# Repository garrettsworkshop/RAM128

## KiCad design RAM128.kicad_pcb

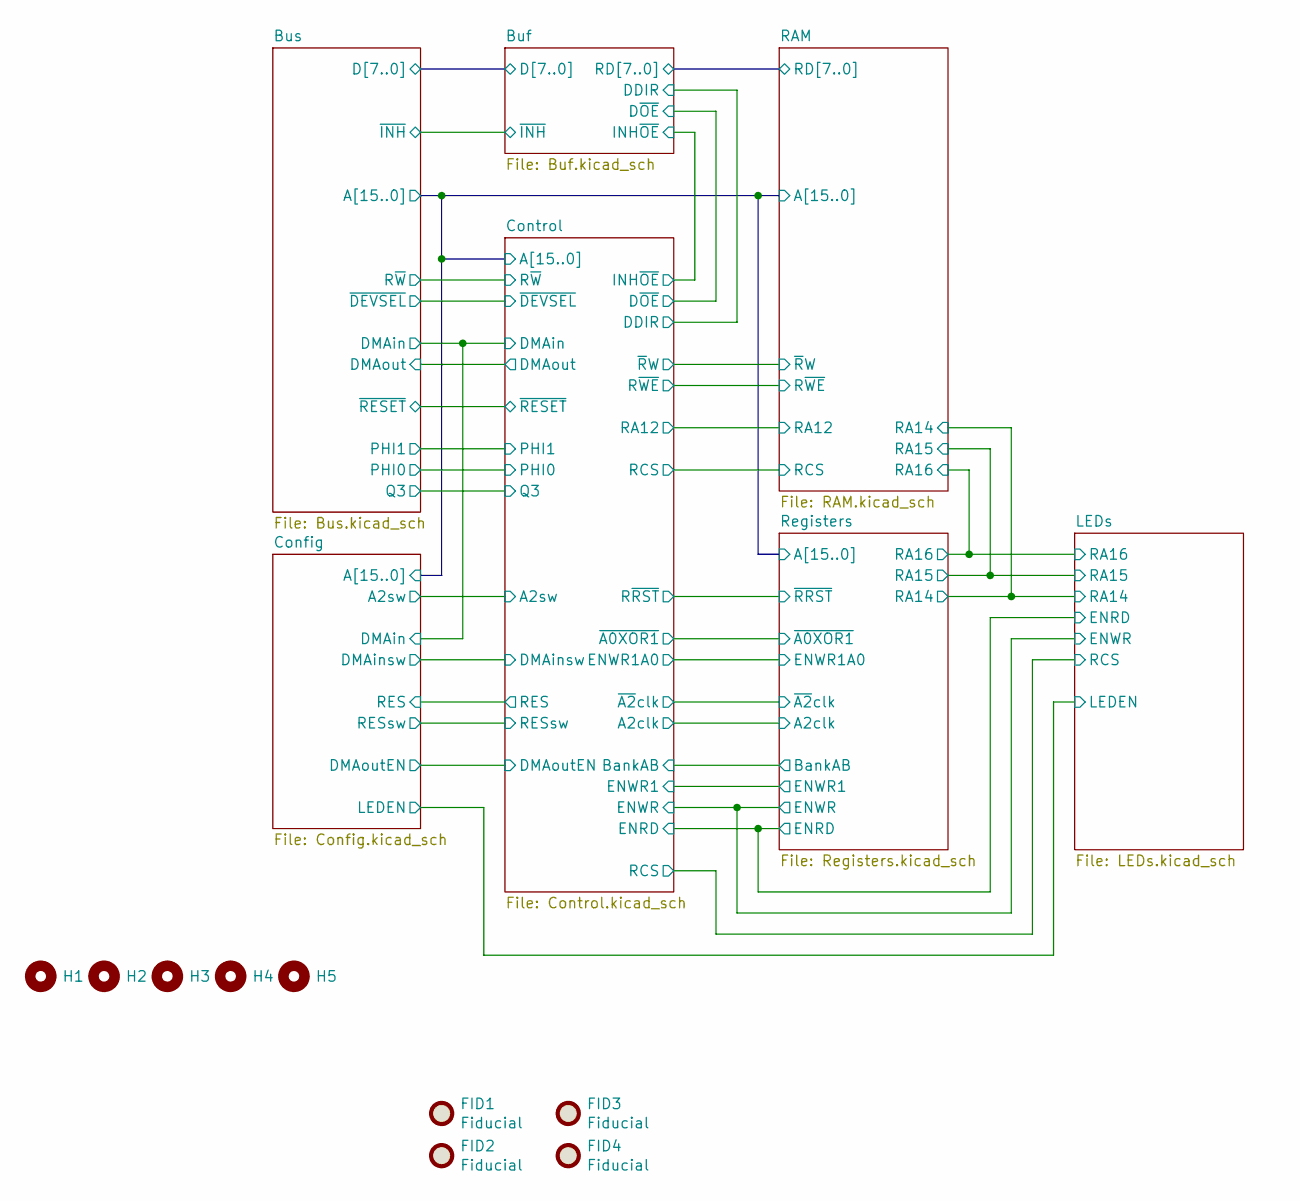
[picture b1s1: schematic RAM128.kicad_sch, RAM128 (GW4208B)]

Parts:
FID1, FID2, FID3, FID4: Fiducial
H1, H2, H3, H4, H5: PasteHole_1.152mm_NPTH

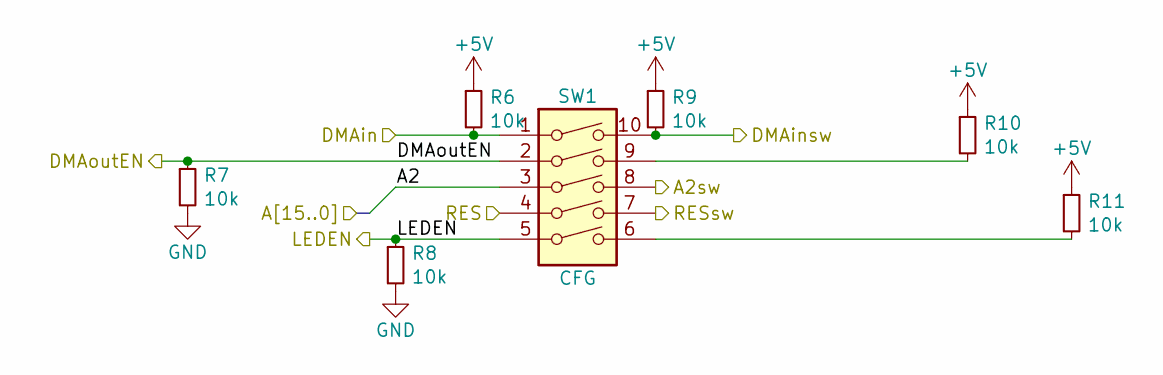
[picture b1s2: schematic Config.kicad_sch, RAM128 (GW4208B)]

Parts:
R6, R7, R8, R9, R10, R11: 10k; R_0603; LCSC Part C17560
SW1: CFG; SW_DIP_SPSTx05_Slide_DSHP05TS_P1.27mm

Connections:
+5V: R6.1, R9.1, R10.1, R11.1; also elsewhere on the board
/Bus/A2: SW1.3; also elsewhere on the board
/Config/A2sw: SW1.8; also elsewhere on the board
/Config/DMAinsw: R9.2, SW1.10; also elsewhere on the board
/Config/DMAoutEN: R7.1, SW1.2; also elsewhere on the board
/Config/LEDEN: R8.1, SW1.5; also elsewhere on the board
/Config/RES: SW1.4; also elsewhere on the board
/Config/RESsw: SW1.7; also elsewhere on the board
/Control/DMAin: R6.2, SW1.1; also elsewhere on the board
GND: R7.2, R8.2; also elsewhere on the board
unnamed: R10.2, SW1.9
unnamed: R11.2, SW1.6

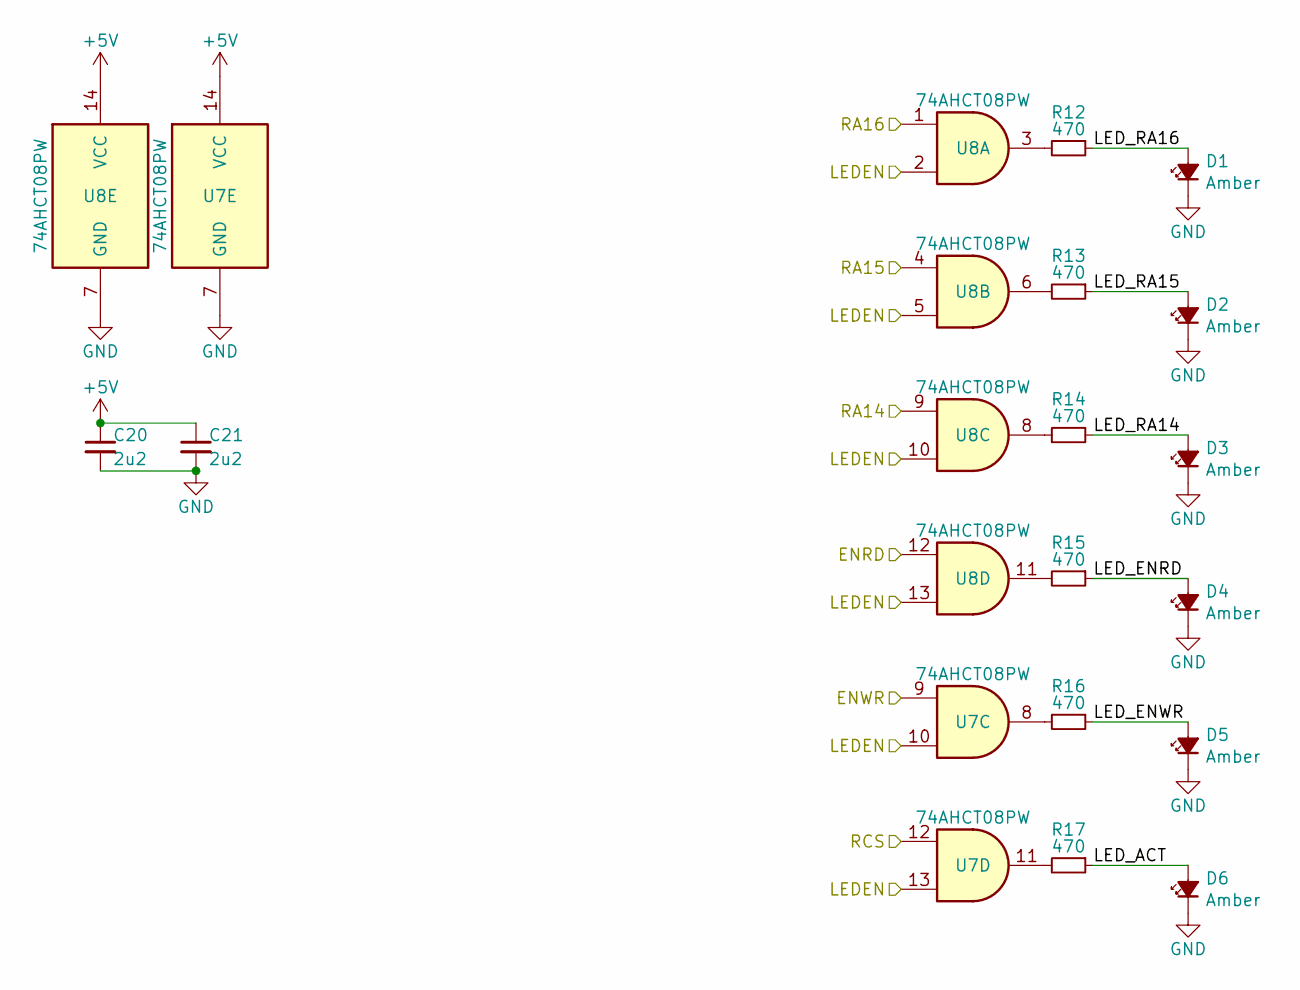
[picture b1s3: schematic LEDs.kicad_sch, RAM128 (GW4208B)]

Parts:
C20, C21: 2u2; C_0603; LCSC Part C23630
D1, D2, D3, D4, D5, D6: Amber; LED_0805; LCSC Part C284932
R12, R13, R14, R15, R16, R17: 470; R_0805
U7, U8: 74AHCT08PW; TSSOP-14_4.4x5mm_P0.65mm; LCSC Part C155175

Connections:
+5V: C20.1, C21.1, U7.14 (VCC), U8.14 (VCC); also elsewhere on the board
/Config/LEDEN: U7.10, U7.13, U8.2, U8.5, U8.10, U8.13; also elsewhere on the board
/Control/ENRD: U8.12; also elsewhere on the board
/Control/ENWR: U7.9; also elsewhere on the board
/Control/RCS: U7.12; also elsewhere on the board
/LEDs/LED_ACT: D6.2 (A), R17.1
/LEDs/LED_ENRD: D4.2 (A), R15.1
/LEDs/LED_ENWR: D5.2 (A), R16.1
/LEDs/LED_RA14: D3.2 (A), R14.1
/LEDs/LED_RA15: D2.2 (A), R13.1
/LEDs/LED_RA16: D1.2 (A), R12.1
/LEDs/RA14: U8.9; also elsewhere on the board
/LEDs/RA15: U8.4; also elsewhere on the board
/LEDs/RA16: U8.1; also elsewhere on the board
GND: C20.2, C21.2, D1.1 (K), D2.1 (K), D3.1 (K), D4.1 (K), D5.1 (K), D6.1 (K), U7.7 (GND), U8.7 (GND); also elsewhere on the board
unnamed: R12.2, U8.3
unnamed: R13.2, U8.6
unnamed: R14.2, U8.8
unnamed: R15.2, U8.11
unnamed: R16.2, U7.8
unnamed: R17.2, U7.11

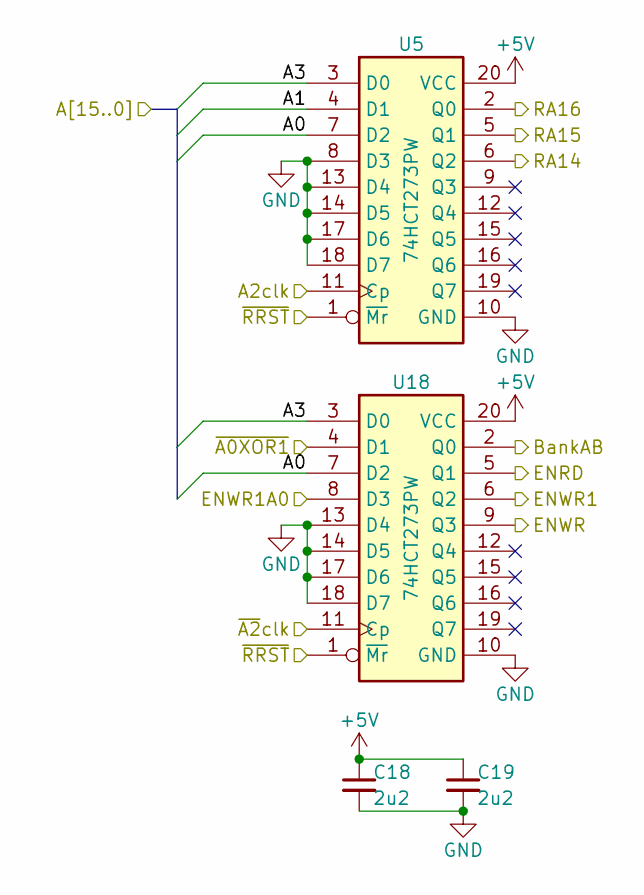
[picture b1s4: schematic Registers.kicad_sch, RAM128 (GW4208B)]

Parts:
C18, C19: 2u2; C_0603; LCSC Part C23630
U5, U18: 74HCT273PW; TSSOP-20_4.4x6.5mm_P0.65mm

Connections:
+5V: C18.1, C19.1, U5.20 (VCC), U18.20 (VCC); also elsewhere on the board
/Bus/A0: U5.7 (D2), U18.7 (D2); also elsewhere on the board
/Bus/A1: U5.4 (D1); also elsewhere on the board
/Bus/A3: U5.3 (D0), U18.3 (D0); also elsewhere on the board
/Control/A2clk: U5.11 (Cp); also elsewhere on the board
/Control/BankAB: U18.2 (Q0); also elsewhere on the board
/Control/ENRD: U18.5 (Q1); also elsewhere on the board
/Control/ENWR: U18.9 (Q3); also elsewhere on the board
/Control/ENWR1: U18.6 (Q2); also elsewhere on the board
/Control/ENWR1A0: U18.8 (D3); also elsewhere on the board
/Control/R~RST: U5.1 (~Mr), U18.1 (~Mr); also elsewhere on the board
/Control/~A0XOR1: U18.4 (D1); also elsewhere on the board
/Control/~A2clk: U18.11 (Cp); also elsewhere on the board
/LEDs/RA14: U5.6 (Q2); also elsewhere on the board
/LEDs/RA15: U5.5 (Q1); also elsewhere on the board
/LEDs/RA16: U5.2 (Q0); also elsewhere on the board
GND: C18.2, C19.2, U5.8 (D3), U5.10 (GND), U5.13 (D4), U5.14 (D5), U5.17 (D6), U5.18 (D7), U18.10 (GND), U18.13 (D4), U18.14 (D5), U18.17 (D6), U18.18 (D7); also elsewhere on the board

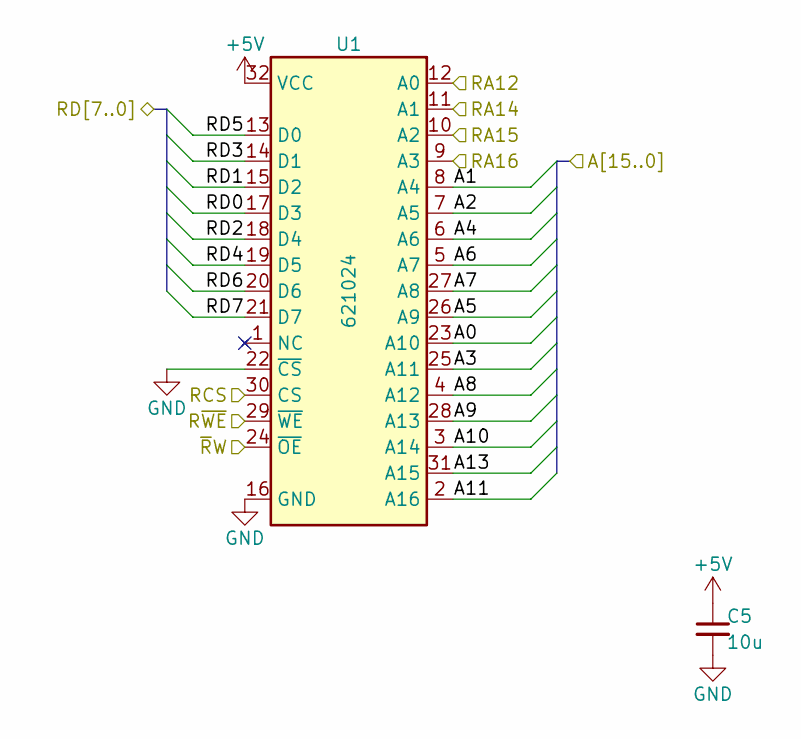
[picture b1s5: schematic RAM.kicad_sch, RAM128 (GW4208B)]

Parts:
C5: 10u; C_0805; LCSC Part C15850
U1: 621024; SOP-32_450mil; LCSC Part C397875

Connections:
+5V: C5.1, U1.32 (VCC); also elsewhere on the board
/Buf/RD0: U1.17 (D3); also elsewhere on the board
/Buf/RD1: U1.15 (D2); also elsewhere on the board
/Buf/RD2: U1.18 (D4); also elsewhere on the board
/Buf/RD3: U1.14 (D1); also elsewhere on the board
/Buf/RD4: U1.19 (D5); also elsewhere on the board
/Buf/RD5: U1.13 (D0); also elsewhere on the board
/Buf/RD6: U1.20 (D6); also elsewhere on the board
/Buf/RD7: U1.21 (D7); also elsewhere on the board
/Bus/A0: U1.23 (A10); also elsewhere on the board
/Bus/A1: U1.8 (A4); also elsewhere on the board
/Bus/A2: U1.7 (A5); also elsewhere on the board
/Bus/A3: U1.25 (A11); also elsewhere on the board
/Bus/A4: U1.6 (A6); also elsewhere on the board
/Bus/A5: U1.26 (A9); also elsewhere on the board
/Bus/A6: U1.5 (A7); also elsewhere on the board
/Bus/A7: U1.27 (A8); also elsewhere on the board
/Bus/A8: U1.4 (A12); also elsewhere on the board
/Bus/A9: U1.28 (A13); also elsewhere on the board
/Bus/A10: U1.3 (A14); also elsewhere on the board
/Bus/A11: U1.2 (A16); also elsewhere on the board
/Bus/A13: U1.31 (A15); also elsewhere on the board
/Control/RA12: U1.12 (A0); also elsewhere on the board
/Control/RCS: U1.30 (CS); also elsewhere on the board
/Control/R~WE: U1.29 (~WE); also elsewhere on the board
/Control/~RW: U1.24 (~OE); also elsewhere on the board
/LEDs/RA14: U1.11 (A1); also elsewhere on the board
/LEDs/RA15: U1.10 (A2); also elsewhere on the board
/LEDs/RA16: U1.9 (A3); also elsewhere on the board
GND: C5.2, U1.16 (GND), U1.22 (~CS); also elsewhere on the board

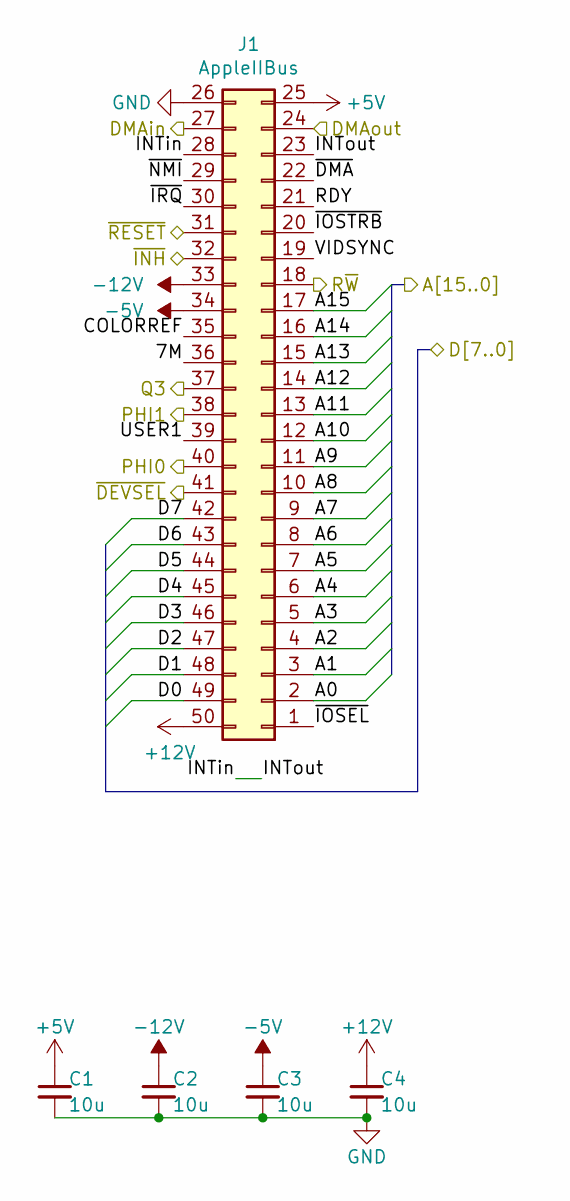
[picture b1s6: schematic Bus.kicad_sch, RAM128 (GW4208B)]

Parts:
C1, C2, C3, C4: 10u; C_0805; LCSC Part C15850
J1: AppleIIBus; AppleIIBus_Edge

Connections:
+5V: C1.1, J1.25; also elsewhere on the board
+12V: C4.1, J1.50
-5V: C3.1, J1.34
-12V: C2.1, J1.33
/Buf/D0: J1.49; also elsewhere on the board
/Buf/D1: J1.48; also elsewhere on the board
/Buf/D2: J1.47; also elsewhere on the board
/Buf/D3: J1.46; also elsewhere on the board
/Buf/D4: J1.45; also elsewhere on the board
/Buf/D5: J1.44; also elsewhere on the board
/Buf/D6: J1.43; also elsewhere on the board
/Buf/D7: J1.42; also elsewhere on the board
/Buf/~INH: J1.32; also elsewhere on the board
/Bus/7M: J1.36
/Bus/A0: J1.2; also elsewhere on the board
/Bus/A1: J1.3; also elsewhere on the board
/Bus/A2: J1.4; also elsewhere on the board
/Bus/A3: J1.5; also elsewhere on the board
/Bus/A4: J1.6; also elsewhere on the board
/Bus/A5: J1.7; also elsewhere on the board
/Bus/A6: J1.8; also elsewhere on the board
/Bus/A7: J1.9; also elsewhere on the board
/Bus/A8: J1.10; also elsewhere on the board
/Bus/A9: J1.11; also elsewhere on the board
/Bus/A10: J1.12; also elsewhere on the board
/Bus/A11: J1.13; also elsewhere on the board
/Bus/A12: J1.14; also elsewhere on the board
/Bus/A13: J1.15; also elsewhere on the board
/Bus/A14: J1.16; also elsewhere on the board
/Bus/A15: J1.17; also elsewhere on the board
/Bus/COLORREF: J1.35
/Bus/DMAout: J1.24; also elsewhere on the board
/Bus/INTin: J1.23, J1.28
/Bus/PHI0: J1.40
/Bus/Q3: J1.37; also elsewhere on the board
/Bus/RDY: J1.21
/Bus/USER1: J1.39
/Bus/VIDSYNC: J1.19
/Bus/~DEVSEL: J1.41; also elsewhere on the board
/Bus/~DMA: J1.22
/Bus/~IOSEL: J1.1
/Bus/~IOSTRB: J1.20
/Bus/~IRQ: J1.30
/Bus/~NMI: J1.29
/Control/DMAin: J1.27; also elsewhere on the board
/Control/PHI1: J1.38; also elsewhere on the board
/Control/R~W: J1.18; also elsewhere on the board
/Control/~RESET: J1.31; also elsewhere on the board
GND: C1.2, C2.2, C3.2, C4.2, J1.26; also elsewhere on the board

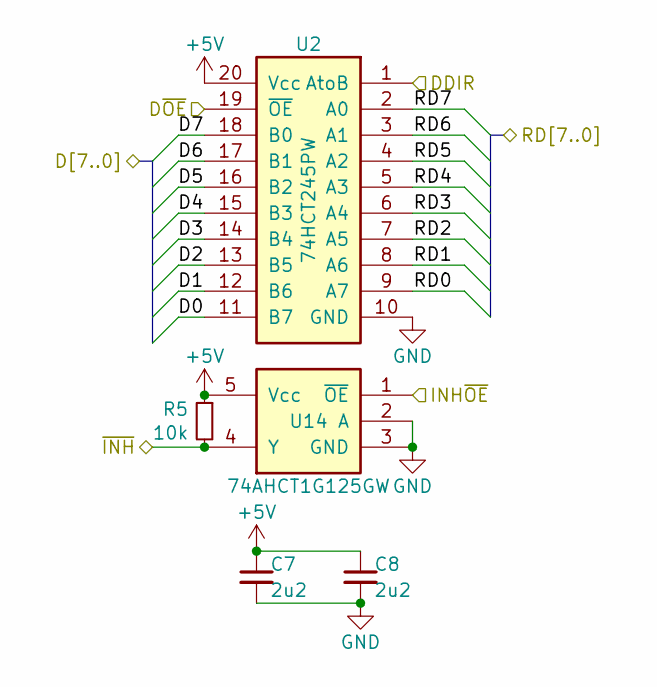
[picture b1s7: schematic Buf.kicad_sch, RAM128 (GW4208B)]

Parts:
C7, C8: 2u2; C_0603; LCSC Part C23630
R5: 10k; R_0603; LCSC Part C17560
U2: 74HCT245PW; TSSOP-20_4.4x6.5mm_P0.65mm; LCSC Part C5980
U14: 74AHCT1G125GW; SOT-353

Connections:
+5V: C7.1, C8.1, R5.1, U2.20 (Vcc), U14.5 (Vcc); also elsewhere on the board
/Buf/D0: U2.11 (B7); also elsewhere on the board
/Buf/D1: U2.12 (B6); also elsewhere on the board
/Buf/D2: U2.13 (B5); also elsewhere on the board
/Buf/D3: U2.14 (B4); also elsewhere on the board
/Buf/D4: U2.15 (B3); also elsewhere on the board
/Buf/D5: U2.16 (B2); also elsewhere on the board
/Buf/D6: U2.17 (B1); also elsewhere on the board
/Buf/D7: U2.18 (B0); also elsewhere on the board
/Buf/DDIR: U2.1 (AtoB); also elsewhere on the board
/Buf/INH~OE: U14.1 (~OE); also elsewhere on the board
/Buf/RD0: U2.9 (A7); also elsewhere on the board
/Buf/RD1: U2.8 (A6); also elsewhere on the board
/Buf/RD2: U2.7 (A5); also elsewhere on the board
/Buf/RD3: U2.6 (A4); also elsewhere on the board
/Buf/RD4: U2.5 (A3); also elsewhere on the board
/Buf/RD5: U2.4 (A2); also elsewhere on the board
/Buf/RD6: U2.3 (A1); also elsewhere on the board
/Buf/RD7: U2.2 (A0); also elsewhere on the board
/Buf/~INH: R5.2, U14.4 (Y); also elsewhere on the board
/Control/D~OE: U2.19 (~OE); also elsewhere on the board
GND: C7.2, C8.2, U2.10 (GND), U14.2 (A), U14.3 (GND); also elsewhere on the board

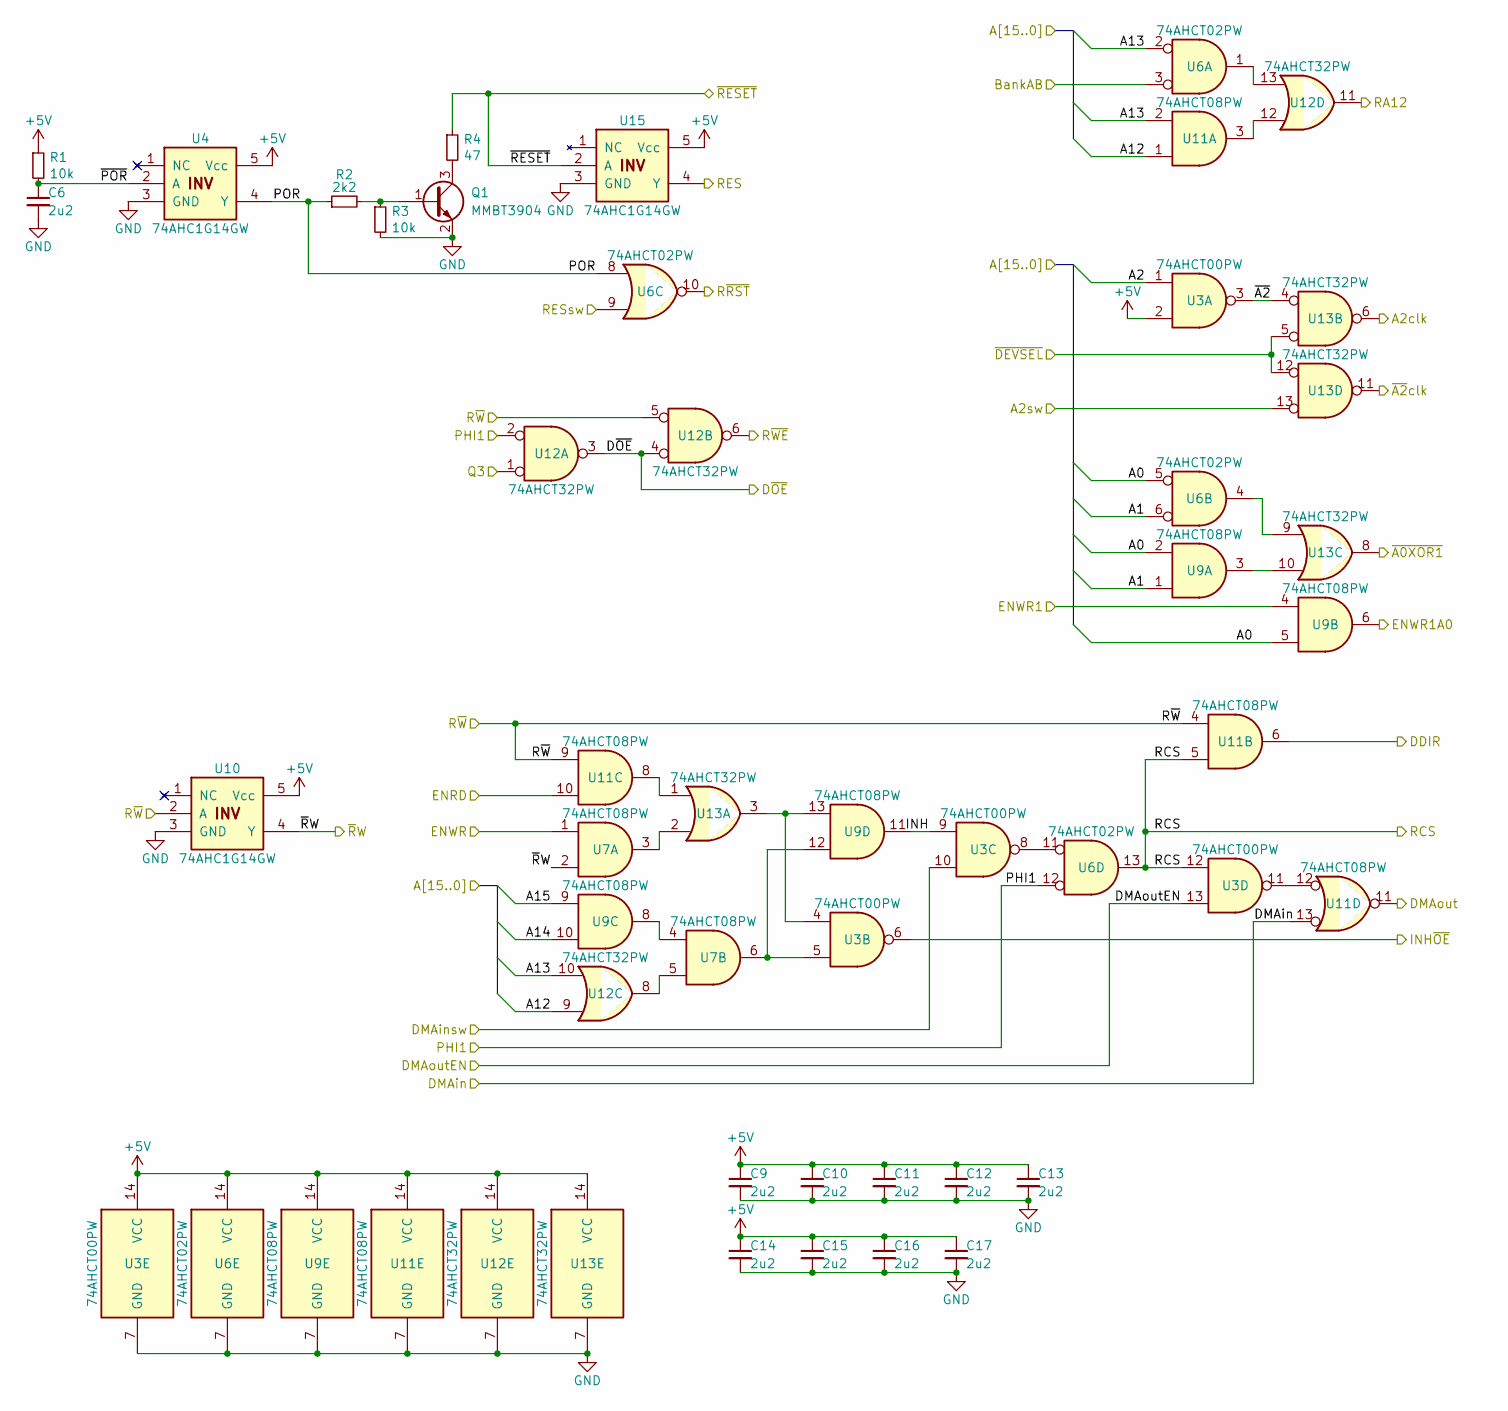
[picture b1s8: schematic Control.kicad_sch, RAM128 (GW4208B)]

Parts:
C6, C9, C10, C11, C12, C13, C14, C15, C16, C17: 2u2; C_0603; LCSC Part C23630
Q1: MMBT3904; SOT-23
R1, R3: 10k; R_0603; LCSC Part C17560
R2: 2k2; R_0603; LCSC Part C17560
R4: 47; R_0603; LCSC Part C17560
U3: 74AHCT00PW; TSSOP-14_4.4x5mm_P0.65mm; LCSC Part C155175
U4, U10, U15: 74AHC1G14GW; SOT-353
U6: 74AHCT02PW; TSSOP-14_4.4x5mm_P0.65mm; LCSC Part C155175
U7, U9, U11: 74AHCT08PW; TSSOP-14_4.4x5mm_P0.65mm; LCSC Part C155175
U12, U13: 74AHCT32PW; TSSOP-14_4.4x5mm_P0.65mm; LCSC Part C129435

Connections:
+5V: C9.1, C10.1, C11.1, C12.1, C13.1, C14.1, C15.1, C16.1, C17.1, R1.1, U3.2, U3.14 (VCC), U4.5 (Vcc), U6.14 (VCC), U9.14 (VCC), U10.5 (Vcc), U11.14 (VCC), U12.14 (VCC), U13.14 (VCC), U15.5 (Vcc); also elsewhere on the board
/Buf/DDIR: U11.6; also elsewhere on the board
/Buf/INH~OE: U3.6; also elsewhere on the board
/Bus/A0: U6.5, U9.2, U9.5; also elsewhere on the board
/Bus/A1: U6.6, U9.1; also elsewhere on the board
/Bus/A2: U3.1; also elsewhere on the board
/Bus/A12: U11.1, U12.9; also elsewhere on the board
/Bus/A13: U6.2, U11.2, U12.10; also elsewhere on the board
/Bus/A14: U9.10; also elsewhere on the board
/Bus/A15: U9.9; also elsewhere on the board
/Bus/DMAout: U11.11; also elsewhere on the board
/Bus/Q3: U12.1; also elsewhere on the board
/Bus/~DEVSEL: U13.5, U13.12; also elsewhere on the board
/Config/A2sw: U13.13; also elsewhere on the board
/Config/DMAinsw: U3.10; also elsewhere on the board
/Config/DMAoutEN: U3.13; also elsewhere on the board
/Config/RES: U15.4 (Y); also elsewhere on the board
/Config/RESsw: U6.9; also elsewhere on the board
/Control/A2clk: U13.6; also elsewhere on the board
/Control/BankAB: U6.3; also elsewhere on the board
/Control/DMAin: U11.13; also elsewhere on the board
/Control/D~OE: U12.3, U12.4; also elsewhere on the board
/Control/ENRD: U11.10; also elsewhere on the board
/Control/ENWR: U7.1; also elsewhere on the board
/Control/ENWR1: U9.4; also elsewhere on the board
/Control/ENWR1A0: U9.6; also elsewhere on the board
/Control/INH: U3.9, U9.11
/Control/PHI1: U6.12, U12.2; also elsewhere on the board
/Control/POR: R2.1, U4.4 (Y), U6.8
/Control/RA12: U12.11; also elsewhere on the board
/Control/RCS: U3.12, U6.13, U11.5; also elsewhere on the board
/Control/R~RST: U6.10; also elsewhere on the board
/Control/R~WE: U12.6; also elsewhere on the board
/Control/R~W: U10.2 (A), U11.4, U11.9, U12.5; also elsewhere on the board
/Control/~A0XOR1: U13.8; also elsewhere on the board
/Control/~A2: U3.3, U13.4
/Control/~A2clk: U13.11; also elsewhere on the board
/Control/~POR: C6.1, R1.2, U4.2 (A)
/Control/~RESET: R4.1, U15.2 (A); also elsewhere on the board
/Control/~RW: U7.2, U10.4 (Y); also elsewhere on the board
GND: C6.2, C9.2, C10.2, C11.2, C12.2, C13.2, C14.2, C15.2, C16.2, C17.2, Q1.2 (E), R3.2, U3.7 (GND), U4.3 (GND), U6.7 (GND), U9.7 (GND), U10.3 (GND), U11.7 (GND), U12.7 (GND), U13.7 (GND), U15.3 (GND); also elsewhere on the board
unnamed: Q1.1 (B), R2.2, R3.1
unnamed: Q1.3 (C), R4.2
unnamed: U3.5, U7.6, U9.12
unnamed: U3.8, U6.11
unnamed: U7.4, U9.8
unnamed: U11.3, U12.12
unnamed: U11.8, U13.1
unnamed: U3.11, U11.12
unnamed: U7.5, U12.8
unnamed: U6.1, U12.13
unnamed: U7.3, U13.2
unnamed: U3.4, U9.13, U13.3
unnamed: U6.4, U13.9
unnamed: U9.3, U13.10

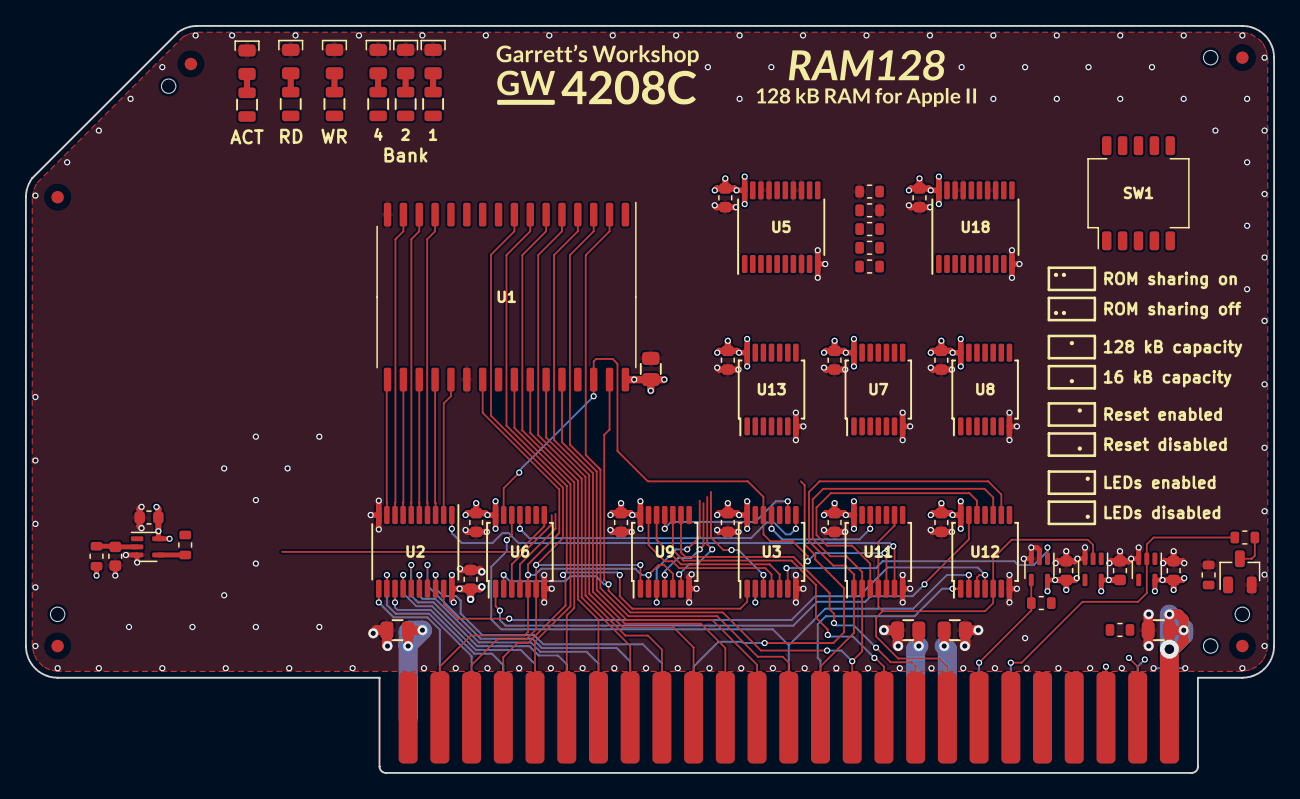
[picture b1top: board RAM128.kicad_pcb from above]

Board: 4 copper layers, 99.9 x 59.8 mm, 73 parts (0 on the bottom side), 103 nets.

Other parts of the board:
FID5: Fiducial

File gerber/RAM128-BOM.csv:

"Reference","Quantity","Value","Footprint","LCSC Part","DNP"
"C1, C2, C3, C4, C5","5","10u","stdpads:C_0805","C15850",""
"C6, C7, C8, C9, C10, C11, C12, C13, C14, C15, C16, C17, C18, C19, C20, C21","16","2u2","stdpads:C_0603","C23630",""
"D1, D2, D3, D4, D5, D6","6","Amber","stdpads:LED_0805","C284932",""
"FID1, FID2, FID3, FID4","4","Fiducial","stdpads:Fiducial","",""
"H1, H2, H3, H4, H5","5","~","stdpads:PasteHole_1.152mm_NPTH","",""
"J1","1","AppleIIBus","stdpads:AppleIIBus_Edge","",""
"Q1","1","MMBT3904","stdpads:SOT-23","",""
"R1, R3, R5, R6, R7, R8, R9, R10, R11","9","10k","stdpads:R_0603","C17560",""
"R2","1","2k2","stdpads:R_0603","C17560",""
"R4","1","47","stdpads:R_0603","C17560",""
"R12, R13, R14, R15, R16, R17","6","470","stdpads:R_0805","",""
"SW1","1","CFG","stdpads:SW_DIP_SPSTx05_Slide_DSHP05TS_P1.27mm","",""
"U1","1","621024","stdpads:SOP-32_450mil","C397875",""
"U2","1","74HCT245PW","stdpads:TSSOP-20_4.4x6.5mm_P0.65mm","C5980",""
"U3","1","74AHCT00PW","stdpads:TSSOP-14_4.4x5mm_P0.65mm","C155175",""
"U4, U10, U15","3","74AHC1G14GW","stdpads:SOT-353","",""
"U5, U18","2","74HCT273PW","stdpads:TSSOP-20_4.4x6.5mm_P0.65mm","",""
"U6","1","74AHCT02PW","stdpads:TSSOP-14_4.4x5mm_P0.65mm","C155175",""
"U7, U8, U9, U11","4","74AHCT08PW","stdpads:TSSOP-14_4.4x5mm_P0.65mm","C155175",""
"U12, U13","2","74AHCT32PW","stdpads:TSSOP-14_4.4x5mm_P0.65mm","C129435",""
"U14","1","74AHCT1G125GW","stdpads:SOT-353","",""

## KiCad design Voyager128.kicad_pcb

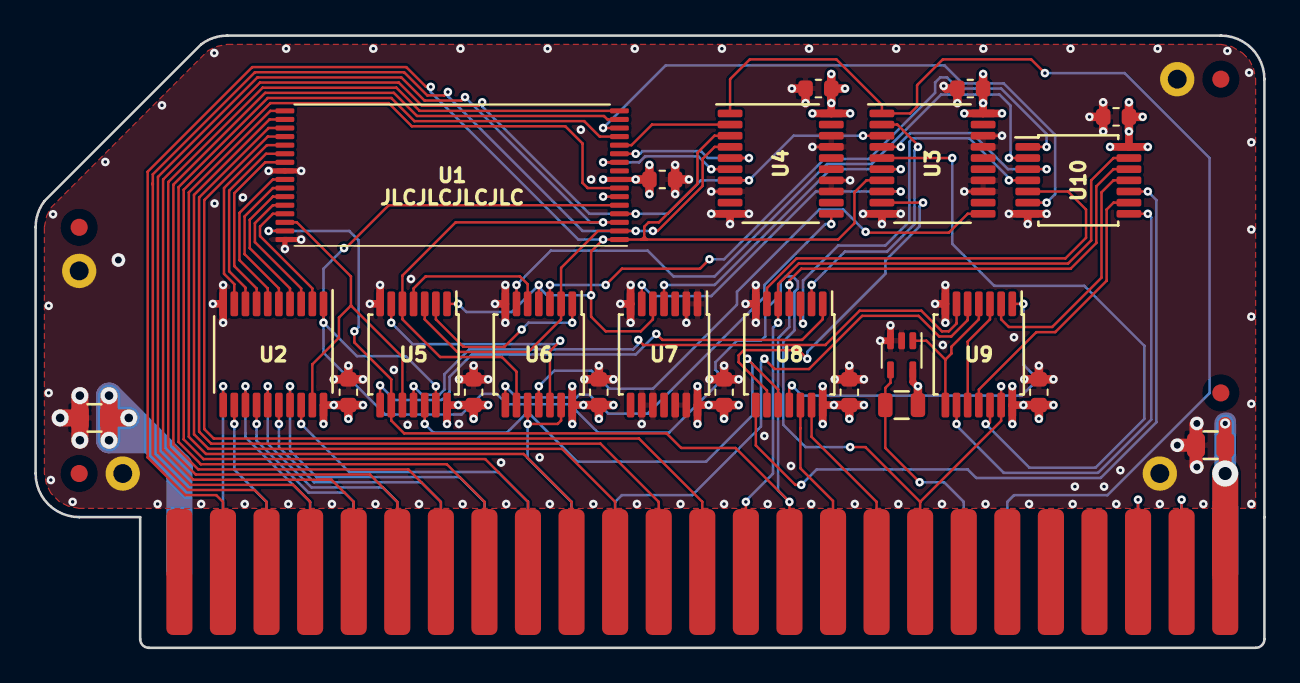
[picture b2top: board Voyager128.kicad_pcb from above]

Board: 4 copper layers, 71.6 x 35.7 mm, 33 parts (0 on the bottom side), 72 nets.

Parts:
C1, C5: 2u2; C_0805
C2, C3, C6, C7, C8, C9, C10, C11, C12, C13: 2u2; C_0603
FID1, FID2, FID4, FID5: Fiducial
H1, H2, H4, H5: PasteHole_1.1mm_PTH
J1: AppleIIBus; AppleIIBus_Edge
R1: 3k3; R_0805
U1: 621024; TSOP-I-32_18.4x8mm_P0.5mm
U2: 74HCT245; TSSOP-20_4.4x6.5mm_P0.65mm
U3, U4: 74LS273; TSSOP-20_4.4x6.5mm_P0.65mm
U5: 74LS04; TSSOP-14_4.4x5mm_P0.65mm
U6, U7, U8, U9: 74LS08; TSSOP-14_4.4x5mm_P0.65mm
U10: 74LS32; TSSOP-14_4.4x5mm_P0.65mm
U11: 74AHC1G126GW; SOT-353

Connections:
+5V: C1.1, C2.1, C3.1, C6.1, C7.1, C8.1, C9.1, C10.1, C11.1, C12.1, C13.1, J1.25, R1.1, U1.6, U1.8, U2.20, U3.20, U4.20, U5.14, U6.14, U7.14, U8.14, U9.14, U10.14, U11.5
+12V: C5.1, J1.50
/A0: J1.2, U1.1, U3.7, U4.3, U5.1, U6.4, U7.5
/A1: J1.3, U1.2, U4.4, U5.3, U6.2
/A2: J1.4, U1.3, U5.5, U6.9
/A3: J1.5, U1.4, U3.3, U4.7
/A4: J1.6, U1.16
/A5: J1.7, U1.15
/A6: J1.8, U1.13
/A7: J1.9, U1.7
/A8: J1.10, U1.17
/A9: J1.11, U1.18
/A10: J1.12, U1.19
/A11: J1.13, U1.20
/A12: J1.14, U8.5, U10.13
/A13: J1.15, U1.31, U5.9, U8.4, U10.12
/A14: J1.16, U8.12
/A15: J1.17, U8.13
/BankAB: U3.2, U8.2
/D0: J1.49, U2.11
/D1: J1.48, U2.12
/D2: J1.47, U2.13
/D3: J1.46, U2.14
/D4: J1.45, U2.15
/D5: J1.44, U2.16
/D6: J1.43, U2.17
/D7: J1.42, U2.18
/DMAin: J1.24, J1.27
/ENRD: U3.5, U9.12
/ENWR: U3.9, U8.9
/ENWR1: U3.6, U7.4
/ENWR1A0: U3.8, U7.6
/INHOE: U9.4, U9.8, U11.1
/INTin: J1.23, J1.28
/PHI0: J1.40, U9.5
/RA12: U1.14, U10.6
/RA14: U1.12, U4.2
/RA15: U1.11, U4.5
/RA16: U1.10, U4.6
/RCS: U5.11, U9.6
/RD0: U1.26, U2.5
/RD1: U1.27, U2.4
/RD2: U1.28, U2.3
/RD3: U1.29, U2.2
/RD4: U1.21, U2.9
/RD5: U1.22, U2.8
/RD6: U1.23, U2.7
/RD7: U1.25, U2.6
/R~CS~: U1.30, U2.19, U5.10
/R~WE~: J1.18, U1.5, U2.1, U5.13, U9.13
/~A0XOR1~: U3.4, U10.3
/~DEVSEL~: J1.41, U6.10, U6.13
/~DEV~andA2: U4.11, U6.8
/~DEV~and~A2~: U3.11, U6.11
/~INH~: J1.32, R1.2, U11.4
/~RES~: J1.31, U3.1, U4.1
GND: C1.2, C2.2, C3.2, C5.2, C6.2, C7.2, C8.2, C9.2, C10.2, C11.2, C12.2, C13.2, H1.1, H2.1, H4.1, H5.1, J1.26, U1.24, U1.32, U2.10, U3.10, U3.13, U3.14, U3.17, U3.18, U4.8, U4.10, U4.13, U4.14, U4.17, U4.18, U5.7, U6.7, U7.1, U7.2, U7.7, U7.9, U7.10, U7.12, U7.13, U8.7, U9.7, U10.7, U11.2, U11.3
unnamed: U5.2, U6.1
unnamed: U5.4, U6.5
unnamed: U5.6, U6.12
unnamed: U5.8, U8.1
unnamed: U5.12, U8.10
unnamed: U8.11, U9.1
unnamed: U9.3, U9.10
unnamed: U6.3, U10.1
unnamed: U6.6, U10.2
unnamed: U8.3, U10.4
unnamed: U8.6, U10.5
unnamed: U9.9, U10.8
unnamed: U9.11, U10.9
unnamed: U8.8, U10.10
unnamed: U9.2, U10.11

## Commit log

2020-07-25 Create LICENSE
2020-07-25 Add GW4208A files
2020-09-10 Board done but ugly
2020-09-10 Remove PAL stuff but keep equations to reference
2020-09-11 Routing done, needs made pretty
2020-09-12 Changed name, updated pictures
2020-09-12 Change file names, delete old pictures, documentation, and geber files
2020-09-12 Add renders
2020-09-12 Update docs
2020-09-12 Update schematic
2020-09-18 Updated manual
2020-09-18 Update manual
2020-09-20 More stitching
2020-09-29 Fixed clock bug
2020-10-09 Fabbed?
2020-10-14 DMA_OUT change
2020-10-22 done with little logic
2020-10-23 little logic done
2020-10-24 Revert "little logic done"
    This reverts commit 1ed2ca3978ceb6b563d39b667c881ffd99cf7564.
2020-10-24 Revert "little logic done"
    This reverts commit a060165095faf621a659fc8f0bd54866ab46c410.
2020-10-24 Revert "done with little logic"
    This reverts commit 274b33dbb27eb7614be9ac524fceba1d77bf04b1.
2020-10-24 Revert "done with little logic"
    This reverts commit e18c2f2ed5eeb331b091e4749a0e5c3a6d648d84.
2020-12-04 Good but ugly
2021-01-06 Fabbed
2021-01-31 Documentation update
2021-02-15 Documentation update for -B revision
2021-04-13 Documentation for GW4208B
2022-02-06 Migrate to KiCAD 6
2022-08-07 As submitted to JLC
2023-01-02 Draft 4208C
2023-11-03 1.1?
2023-11-07 Update Makefile
2023-11-27 1.2?
2023-12-07 1.2 prototype as sent to JLC
2023-12-07 Update schematic and PCB version and revision date
2023-12-16 Remove render photo blobs
2024-01-07 1.2 RC2
2024-01-31 1.2 RC3
    Moved 621024 bypass cap over--that's it
2024-02-01 1.2 RC4
2024-03-03 Update Makefile
    Delete old gerber zip file before rezipping
2024-03-03 Add BOM export and rebuild. No board changes
2024-03-03 Update Makefile
    Reorganize slightly
2024-03-03 Update BOM, no board changes
2024-03-18 Adopt 0.5mm via-to-via spacing
2024-03-29 RC 1.3
2025-02-15 consolidate logic
2025-03-30 schematic and placement done?
2025-04-28 more
